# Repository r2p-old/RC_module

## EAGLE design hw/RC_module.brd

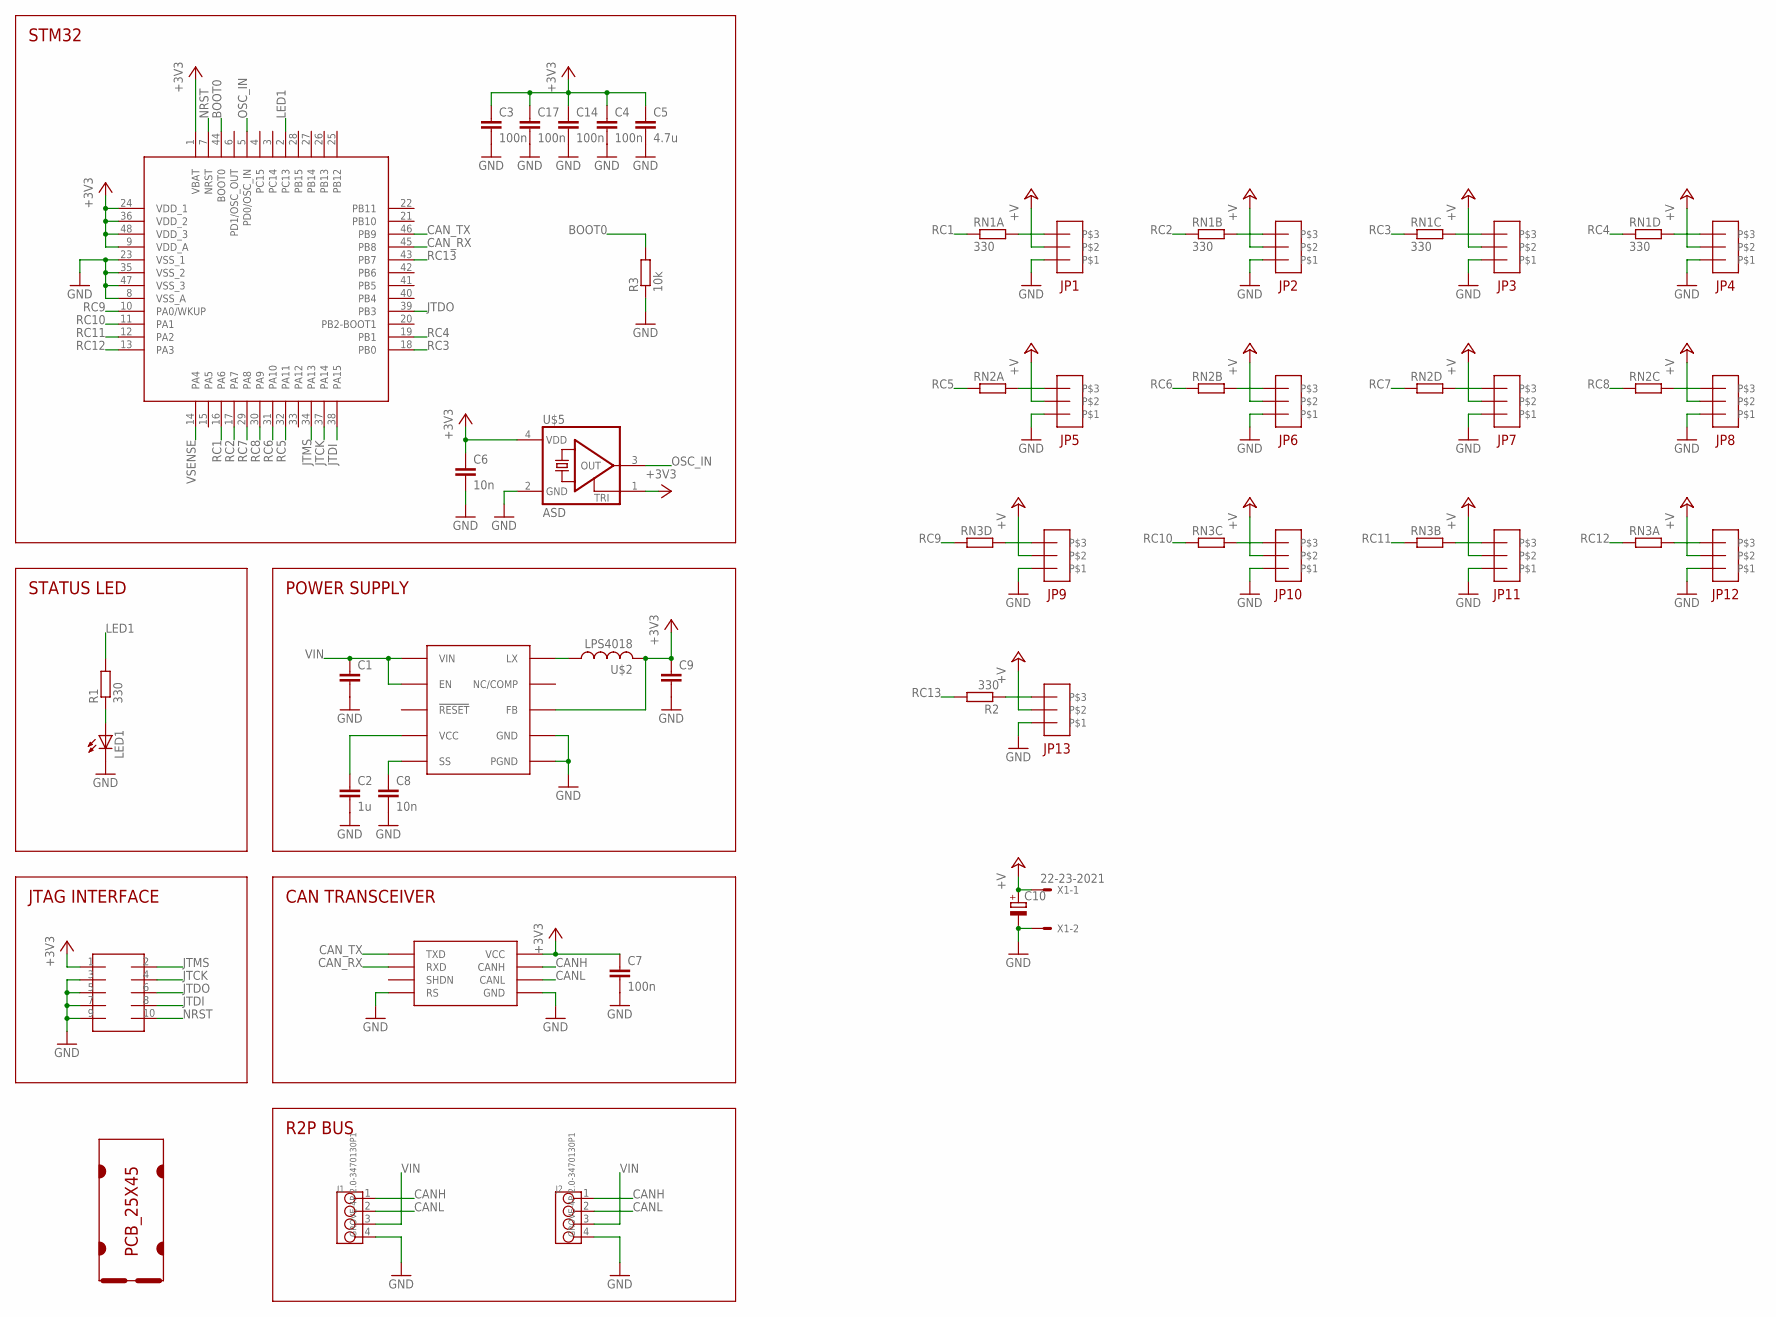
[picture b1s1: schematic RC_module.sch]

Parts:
C1: C-EUC1206; C1206
C2: 1u; C0603
C3, C4, C7, C14, C17: 100n; C0603
C5: 4.7u; C0805
C6, C8: 10n; C0603
C9: C-EUC0805; C0805
C10: CPOL-EUB/3528-21R; B/3528-21R
J1, J2: GROVE-4P-2.0-3470130P1; 4P-2.0
JP1, JP2, JP3, JP4, JP5, JP6, JP7, JP8, JP9, JP10, JP11, JP12, JP13: PINHD-3; 1X03
LED1: LEDCHIPLED_0805; CHIPLED_0805
R1, R2: 330; R0603
R3: 10k; R0603
RN1: 330; RN8P-4R-CRA06S
RN2, RN3: RESISTOR_ARRAY_4; RN8P-4R-CRA06S
SOT1: MAX3051EKA; SOT23-8L
U$1: PCB_25X45; 25X45
U$2: LPS4018
U$3: MAX17501; TDFN-10
U$4: FTSH-105TH; FTSH-105-TH
U$5: ASD; 2.5X2
U$6: STM32F103CX; LQFP48
X1: 22-23-2021

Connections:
+3V3: C3.1, C4.1, C5.1, C6.1, C7.1, C9.1, C14.1, C17.1, SOT1.3 (VCC), U$2.P$2 (2), U$3.P$5 (FB), U$4.1, U$5.1 (TRI), U$5.4 (VDD), U$6.1 (VBAT), U$6.9 (VDD_A), U$6.24 (VDD_1), U$6.36 (VDD_2), U$6.48 (VDD_3)
+V: C10.+, JP1.2, JP2.2, JP3.2, JP4.2, JP5.2, JP6.2, JP7.2, JP8.2, JP9.2, JP10.2, JP11.2, JP12.2, JP13.2, X1.1
BOOT0: R3.2, U$6.44 (BOOT0)
CANH: J1.1, J2.1, SOT1.7 (CANH)
CANL: J1.2, J2.2, SOT1.6 (CANL)
CAN_RX: SOT1.4 (RXD), U$6.45 (PB8)
CAN_TX: SOT1.1 (TXD), U$6.46 (PB9)
GND: C1.2, C2.2, C3.2, C4.2, C5.2, C6.2, C7.2, C8.2, C9.2, C10.-, C14.2, C17.2, J1.4, J2.4, JP1.1, JP2.1, JP3.1, JP4.1, JP5.1, JP6.1, JP7.1, JP8.1, JP9.1, JP10.1, JP11.1, JP12.1, JP13.1, LED1.C, R3.1, SOT1.2 (GND), SOT1.8 (RS), U$3.P$1 (PGND), U$3.P$9 (GND), U$3.P$11 (PGND), U$4.3, U$4.5, U$4.7, U$4.9, U$5.2 (GND), U$6.8 (VSS_A), U$6.23 (VSS_1), U$6.35 (VSS_2), U$6.47 (VSS_3), X1.2
JTCK: U$4.4, U$6.37 (PA14)
JTDI: U$4.8, U$6.38 (PA15)
JTDO: U$4.6, U$6.39 (PB3)
JTMS: U$4.2, U$6.34 (PA13)
LED1: R1.2, U$6.2 (PC13)
unnamed: U$2.P$1 (1), U$3.P$10 (LX)
unnamed: LED1.A, R1.1
unnamed: JP12.3, RN3.8 (2)
unnamed: C2.1, U$3.P$4 (VCC)
unnamed: C8.1, U$3.P$6 (SS)
unnamed: JP6.3, RN2.7 (2)
unnamed: JP7.3, RN2.5 (2)
unnamed: JP5.3, RN2.8 (2)
unnamed: JP1.3, RN1.8 (2)
unnamed: JP9.3, RN3.5 (2)
unnamed: JP10.3, RN3.6 (2)
unnamed: JP11.3, RN3.7 (2)
unnamed: JP13.3, R2.1
unnamed: JP2.3, RN1.7 (2)
unnamed: JP3.3, RN1.6 (2)
unnamed: JP8.3, RN2.6 (2)
unnamed: JP4.3, RN1.5 (2)
NRST: U$4.10, U$6.7 (NRST)
OSC_IN: U$5.3 (OUT), U$6.5 (PD0/OSC_IN)
RC1: RN1.1, U$6.16 (PA6)
RC2: RN1.2 (1), U$6.17 (PA7)
RC3: RN1.3 (1), U$6.18 (PB0)
RC4: RN1.4 (1), U$6.19 (PB1)
RC5: RN2.1, U$6.32 (PA11)
RC6: RN2.2 (1), U$6.31 (PA10)
RC7: RN2.4 (1), U$6.29 (PA8)
RC8: RN2.3 (1), U$6.30 (PA9)
RC9: RN3.4 (1), U$6.10 (PA0/WKUP)
RC10: RN3.3 (1), U$6.11 (PA1)
RC11: RN3.2 (1), U$6.12 (PA2)
RC12: RN3.1, U$6.13 (PA3)
RC13: R2.2, U$6.43 (PB7)
VIN: C1.1, J1.3, J2.3, U$3.P$2 (VIN), U$3.P$3 (EN)
VSENSE: U$6.14 (PA4)

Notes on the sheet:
STM32
STATUS LED
JTAG INTERFACE
POWER SUPPLY
CAN TRANSCEIVER
R2P BUS

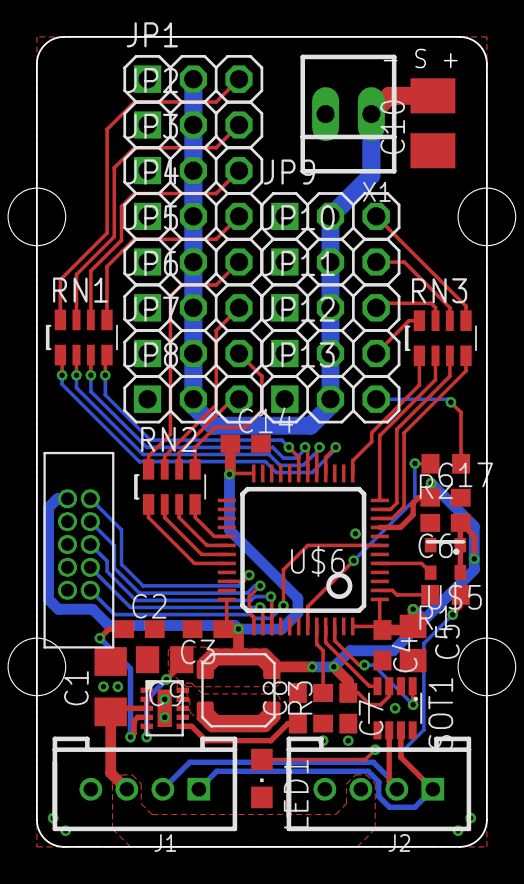
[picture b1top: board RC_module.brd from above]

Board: 2 copper layers, 25.0 x 45.0 mm, 42 parts (0 on the bottom side), 46 nets.

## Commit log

2014-05-29 layout completed
2014-06-04 added gitignore to tracked files
2014-06-23 Added makefile for quicker gerber generation
2014-06-24 added PNG of board layout
2014-08-01 added R values
2014-12-16 small fixes
2014-12-29 approved DRC false errors
2015-01-08 added logo to bottom silkscreen
